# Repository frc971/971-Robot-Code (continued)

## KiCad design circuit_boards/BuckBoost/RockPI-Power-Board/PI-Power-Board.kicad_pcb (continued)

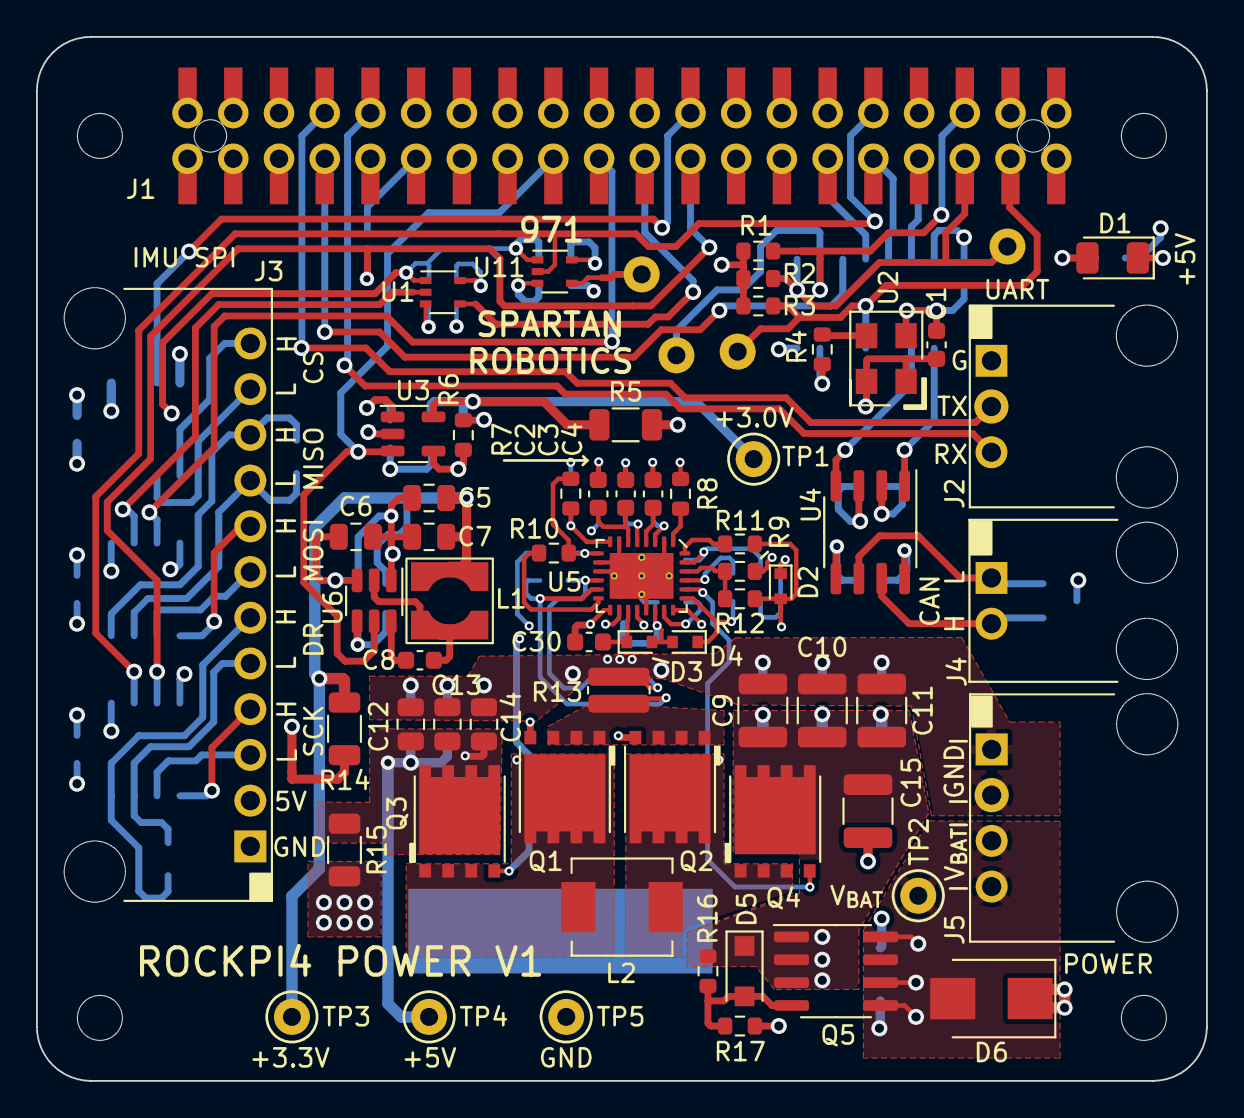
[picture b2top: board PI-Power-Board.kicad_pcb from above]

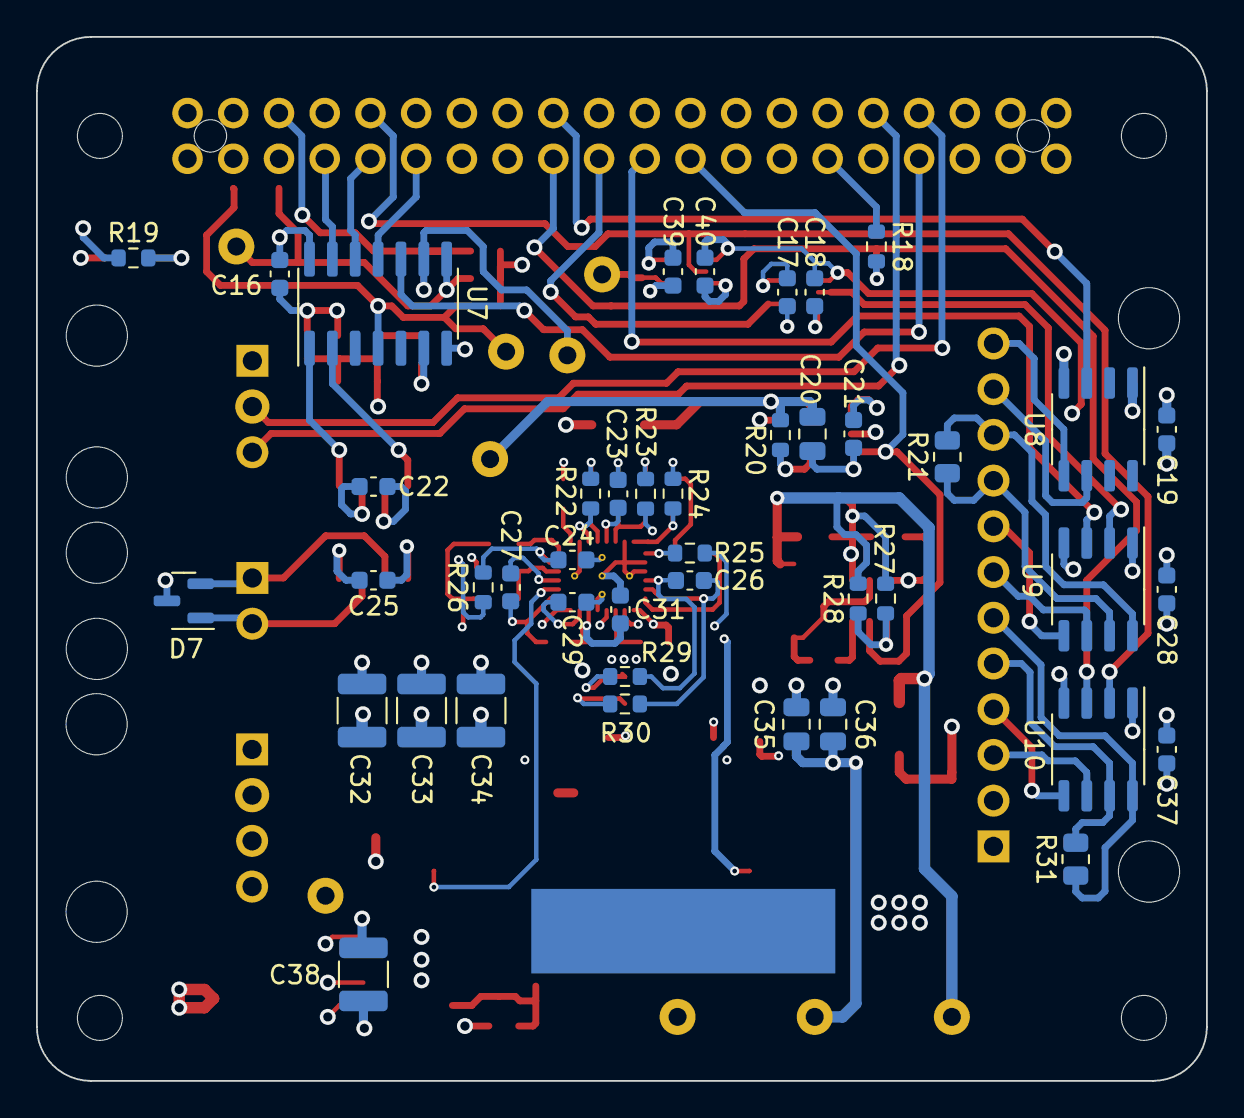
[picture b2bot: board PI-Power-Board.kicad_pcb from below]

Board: 4 copper layers, 65.0 x 58.0 mm, 118 parts (43 on the bottom side), 74 nets.

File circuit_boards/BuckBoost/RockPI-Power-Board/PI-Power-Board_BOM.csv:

Source:,/home/scottberman/Documents/Projects/FRC971/RKPI4-Power/PI-Power-Board/PI-Power-Board.kicad_sch,,,,
Date:,Tue 06 Dec 2022 05:25:53 PM PST,,,,
Tool:,Eeschema 6.0.9-8da3e8f707~117~ubuntu20.04.1,,,,
Generator:,/usr/share/kicad/plugins/bom_csv_grouped_by_value.py,,,,
Component Count:,103,,,,
,,,,,
Individual Components:,,,,,
,,,,,
,,,,,
Item,Qty,Reference(s),Value,MFG,MFG P/N
1,17,"C1, C8, C16, C17, C18, C19, C21, C22, C24, C25, C27, C28, C29, C30, C37, C39, C40",0.1uF-10%-50V-0603,Samsung Electro-Mechanics,CL10B104KB8NNNC
2,2,"C2, C23",0.015uF-10%-50V-0603,YAGEO,CC0603KRX7R9BB153
3,1,C3,330pF-5%-50V-0603,Murata,GCM1885C2A331FA16D
4,2,"C4, C26",47pF-5%-50V-0603,Samsung Electro-Mechanics,CL10C470JB8NNNC
5,9,"C5, C6, C7, C12, C13, C14, C20, C35, C36",22uF-10V-10%-0805,Samsung Electro-Mechanics,CL21A226KPCLRNC
6,8,"C9, C10, C11, C15, C32, C33, C34, C38",22uF-25V-10%-1210,Murata,GRM32ER61E226KE15L
7,1,C31,1.0uF-10%-10V-0603,Samsung Electro-Mechanics,CL10B105KP8NNNC
8,1,D1,+5V,Everlight Electronics Co Ltd,QTLP650D4TR
9,1,D2,NSR05T40XV2T5G,onsemi,NSR05T40XV2T5G
10,1,D3,NSR05T40XV2T5G,onsemi,NSR05T40XV2T5G
11,1,D4,NSR05T40XV2T5G,onsemi,NSR05T40XV2T5G
12,1,D5,15V,Nexperia,"BZT52H-C15,115"
13,1,D6,15V,Littelfuse,SZ1SMB15CAT3G
14,1,D7,PESD1CAN,Nexperia,"PESD1CAN,215"
15,1,J1,PI Header,Harwin Inc,M20-7812045
16,1,J2,UART,Molex,70555-0002
17,1,J3,IMU SPI,Molex,70555-0011
18,1,J4,CAN,Molex,70555-0001
19,1,J5,POWER,Molex,70555-0003
20,1,L1,2.5uH-1.45A,Wurth Electronik,744031002
21,1,L2,1.0 uH-13.7m-20%,Vishay,IHLP2020CZER1R0M01
22,4,"Q1, Q2, Q3, Q4",CSD17577Q5A,Texas Instruments,CSD17577Q5A
23,1,Q5,SI4483ADY-T1-GE3,Vishay,SI4483ADY-T1-GE3
24,5,"R1, R2, R3, R9, R23",2.00k-1%-0603,Yageo,RC0603FR-072KL
25,1,R4,49.9R-1%-0603,Yageo,RC0603FR-0749R9L
26,3,"R5, R14, R15",0R-1206,Yageo,RC1206JR-070RL
27,2,"R6, R20",DNI-0603,,
28,2,"R7, R11",105k-1%-0603,Yageo,RC0603FR-07105KL
29,1,R8,93.1k-1%-0603,Panasonic Electronic Components,ERJ-3EKF9312V
30,1,R10,10K0-1%-0603,Yageo,RC0603FR-0710KL
31,1,R12,249k-1%-0603,Yageo,RC0603FR-07249KL
32,1,R13,15m-1%-0612,"KOA Speer Electronics, Inc.",WU732BTTD15L0F
33,2,"R16, R24",20.0k-1%-0603,Yageo,RC0603FR-0720KL
34,2,"R17, R19",1.0k-1%-0603,Yageo,RC0603FR-071KL
35,1,R18,499R-1%-0603,Yageo,RC0603FR-07499RL
36,2,"R21, R31",120R-1%-0805,Yageo,RMCF0805FT120R
37,1,R22,15.8k-1%-0603,Yageo,RC0603FR-0715K8L
38,1,R25,0R-0603,Stackpole Electronics Inc,RMCF0603ZT0R00
39,1,R26,10R0-1%-0603,Yageo,RC0603FR-0710RL
40,1,R27,31.6k-1%-0603,Stackpole Electronics Inc,RMCF0603FT31K6
41,1,R28,10.0k-1%-0603,Yageo,RC0603FR-0710KL
42,2,"R29, R30",100R-1%-0603,Yageo,RC0603FR-07100RL
43,5,"TP1, TP2, TP3, TP4, TP5",,Keystone Electronics,5002
48,2,"U1, U11",NLSV1T34DFT2G,onsemi,NLSV1T34DFT2G
49,1,U2,40MHz,ECS Inc,ECS-5032MV-400-CN-TR
50,1,U3,MIC5233-3.0YM5-TR,Microchip,MIC5233-3.0YM5-TR
51,1,U4,MCP2542FD-E/SN,Microchip,MCP2542FD-E/SN
52,1,U5,LM5176RHF,Texas Instruments,LM5176RHFT
53,1,U6,AP62200WU-7,Diodes Inc,AP62200WU-7
54,1,U7,MCP2517FDT-H/SL,Microchip,MCP2517FDT-H/SL
55,3,"U8, U9, U10",ADM3490ARZ,Analog Devices,ADM3490ARZ

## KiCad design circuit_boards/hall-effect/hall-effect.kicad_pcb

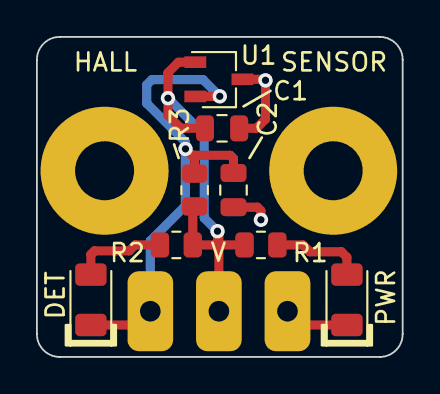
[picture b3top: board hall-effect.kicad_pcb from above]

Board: 2 copper layers, 20.3 x 17.8 mm, 11 parts (0 on the bottom side), 5 nets.

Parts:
C1: 0.1uF-25V-0805; C_0805_2012Metric
C2: 4.7nF-50V-0805; C_0805_2012Metric
D1: PWR; LED_1206_3216Metric
D2: DET; LED_1206_3216Metric
H1, H2: mounting-hole
J1: Conn_01x03_Male; 3PIN header
R1, R2: 1.0k-1%-0805; R_0805_2012Metric
R3: 10k-1%-0805; R_0805_2012Metric
U1: US5881LSE; TSOT-23

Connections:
/5V0: C1.1, J1.2, R1.1, R2.1, R3.1, U1.1 (VDD)
/GND: C1.2, C2.2, D1.1 (K), J1.1, U1.3 (GND)
/OUT: C2.1, D2.1 (K), J1.3, R3.2, U1.2 (OUT)
unnamed: D1.2 (A), R1.2
unnamed: D2.2 (A), R2.2

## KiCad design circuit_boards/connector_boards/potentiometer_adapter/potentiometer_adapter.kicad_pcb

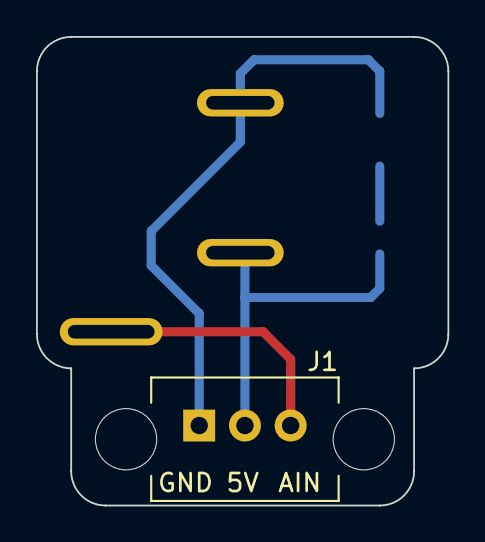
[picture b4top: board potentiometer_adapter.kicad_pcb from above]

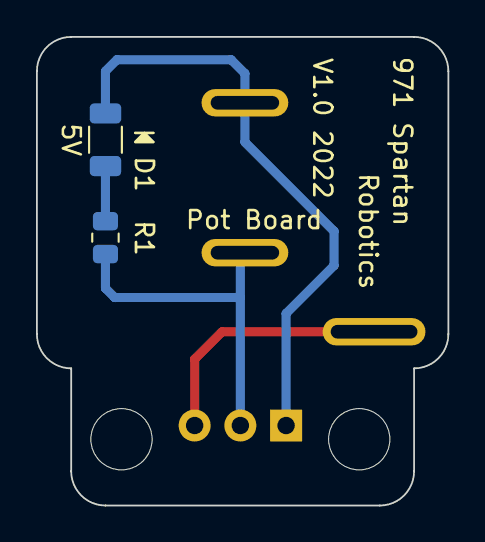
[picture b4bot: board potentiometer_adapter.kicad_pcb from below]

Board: 2 copper layers, 22.9 x 26.0 mm, 4 parts (2 on the bottom side), 4 nets.

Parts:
D1: 5V; R_1206_3216Metric
J1: Conn_01x03_Male; 70541-0037
R1: 2K 1%; R_0805_2012Metric
RV1: R_Potentiometer; Bourns3647

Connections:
/5V0: J1.2, R1.1, RV1.1
/AIN: J1.3, RV1.2
/GND: D1.1 (K), J1.1, RV1.3
unnamed: D1.2 (A), R1.2

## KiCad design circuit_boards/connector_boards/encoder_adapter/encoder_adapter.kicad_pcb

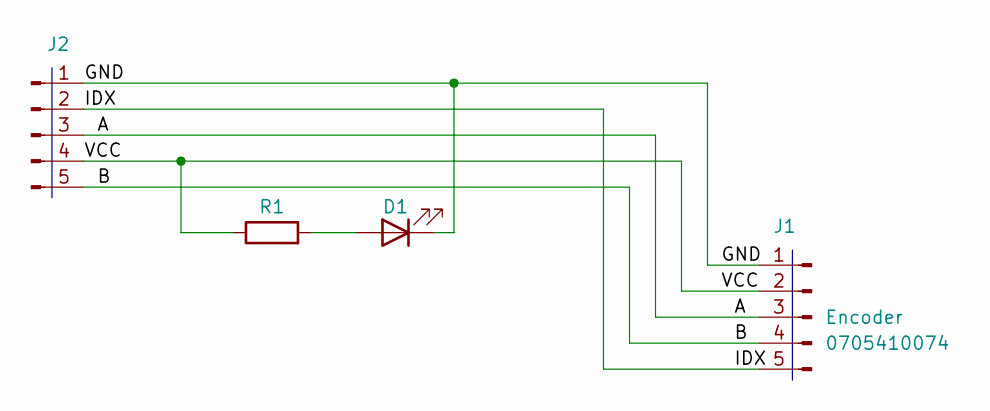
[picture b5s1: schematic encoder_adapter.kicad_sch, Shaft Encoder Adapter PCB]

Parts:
D1: LED; LED_1206_3216Metric; MFG P/N QTLP650D4TR
J1: Encoder; MOLEX_0705410074; MFG P/N 0705410074
J2: Conn_01x05_Male; PinHeader_1x05_P2.54mm_Vertical
R1: R; R_0805_2012Metric

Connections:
/A: J1.3, J2.3
/B: J1.4, J2.5
/GND: D1.1 (K), J1.1, J2.1
/IDX: J1.5, J2.2
/VCC: J1.2, J2.4, R1.1
unnamed: D1.2 (A), R1.2

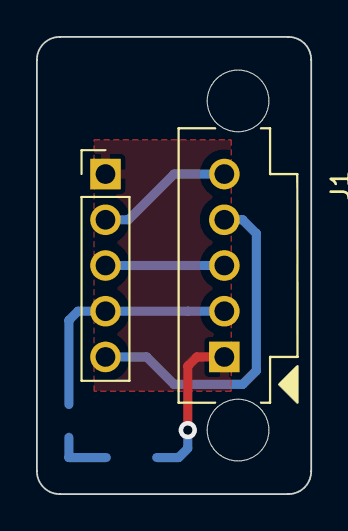
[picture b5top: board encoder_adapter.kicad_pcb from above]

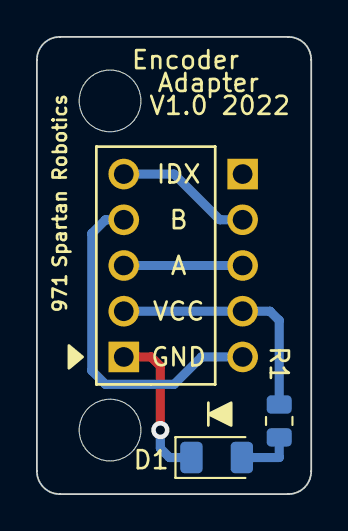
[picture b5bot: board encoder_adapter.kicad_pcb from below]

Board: 2 copper layers, 15.2 x 25.4 mm, 4 parts (2 on the bottom side), 6 nets.

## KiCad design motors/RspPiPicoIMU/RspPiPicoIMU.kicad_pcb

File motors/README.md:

# Driver station
## Setup
1. Install Teensy Loader [here](https://www.pjrc.com/teensy/loader_mac.html).

## Make changes
1. Most of the code lives in `/motors/driver_station*`.

## Deploy
1. Build driver station. This outputs a file `bazel-bin/motors/driver_station.hex`.
    ```shell
    bazel build -c opt --config=cortex-m4f //motors:driver_station
    ```

2. Send the file to your local development machine.
    ```shell
    scp <user@build.frc971.org>:917-Robot-Code/bazel-bin/motors/driver_station.hex ~/Downloads/driver_station.hex
    ```

3. Open hex file in Teensy loader. Press button on Teensy.

## Swerve
1. To allow a swerve controller to work, a jumper should be in the BTN17 spot (view schematics below).

## References
- Electrical schematics [here](https://github.com/frc971/electrical/blob/main/robots/2023/driver-station/DriverStation-8Apr2023.pdf).
- Joystick adc pin mapping[here](https://github.com/frc971/electrical/blob/main/robots/2025/Driver%20Station/Harness%20Drawings/TX16S-Joystick-Input.png).

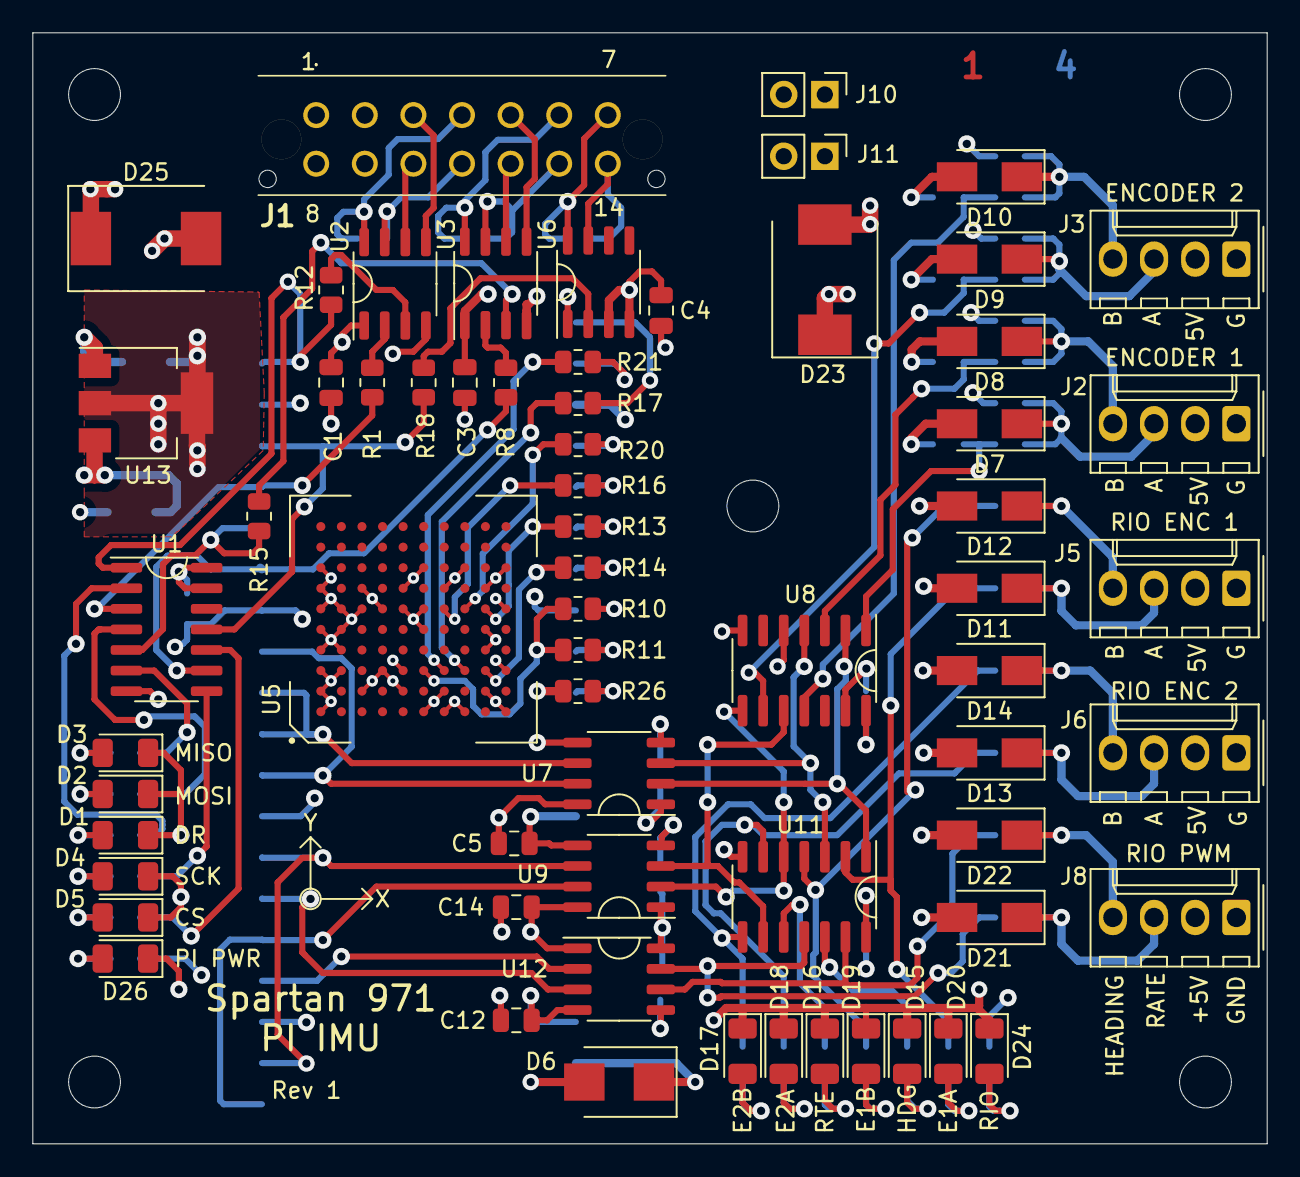
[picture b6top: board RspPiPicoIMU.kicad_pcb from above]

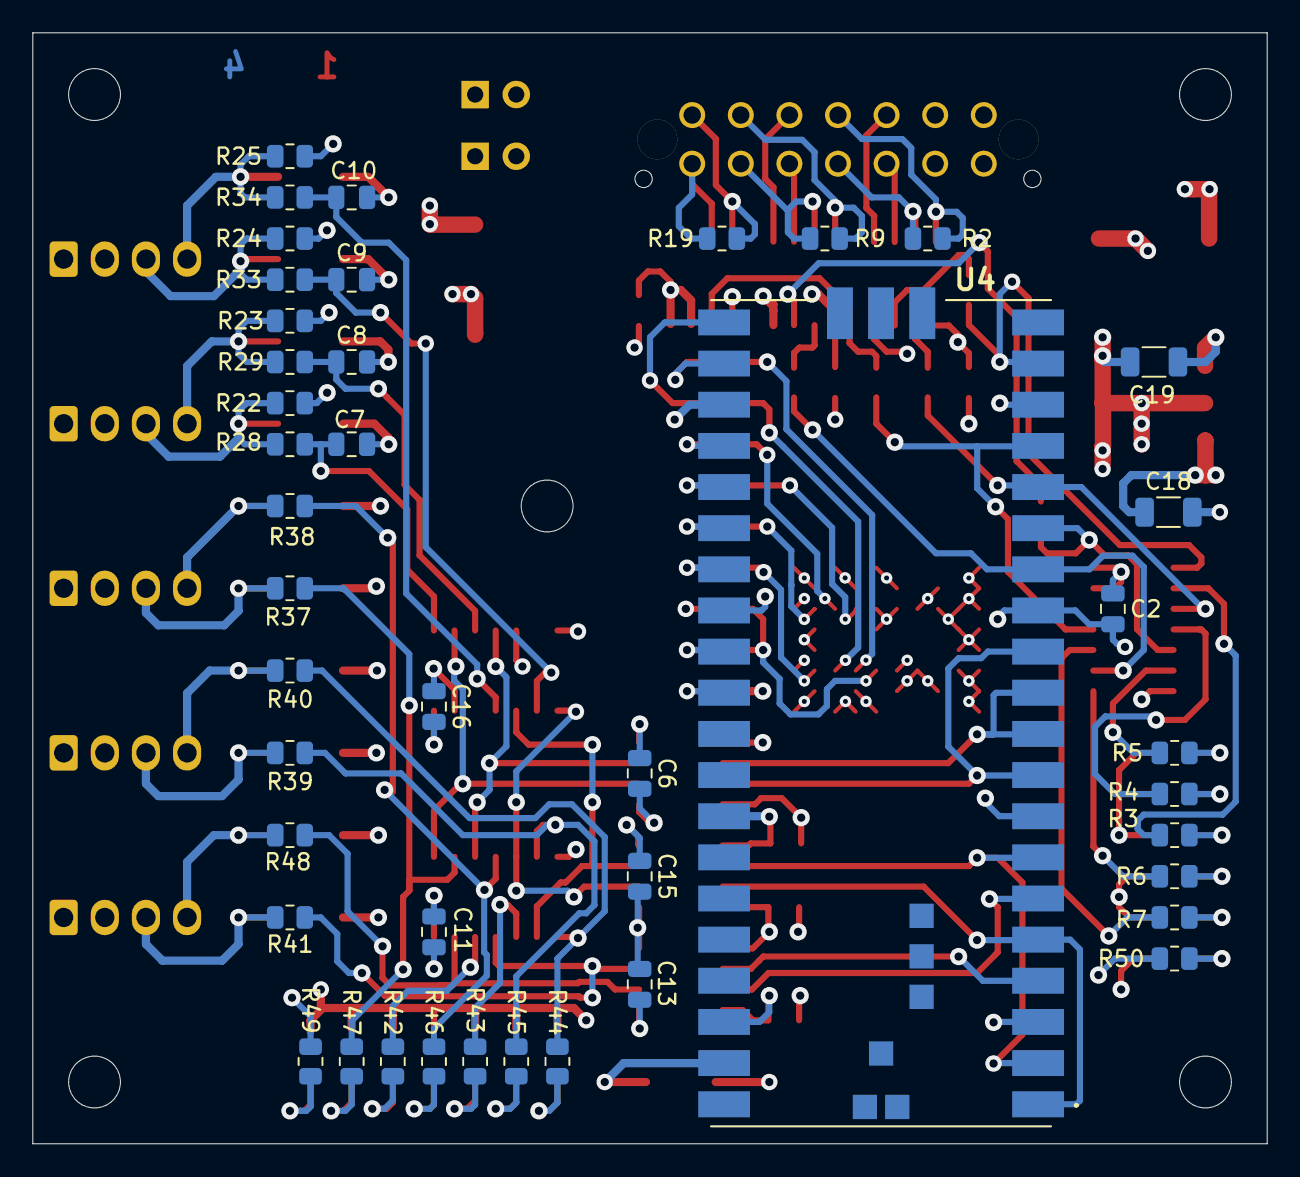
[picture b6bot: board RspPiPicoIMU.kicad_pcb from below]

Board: 4 copper layers, 76.2 x 68.6 mm, 113 parts (43 on the bottom side), 91 nets.

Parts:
C1, C2, C3, C4, C5, C6, C11, C12, C13, C14, C15, C16: 0.1uF; C_0805_2012Metric
C7, C8, C9, C10: 1.0nF; C_0805_2012Metric
C18, C19: 22uF; C_1206_3216Metric
D1: DR; LED_1206_3216Metric
D2: MOSI; LED_1206_3216Metric
D3: MISO; LED_1206_3216Metric
D4: SCK; LED_1206_3216Metric
D5: CS; LED_1206_3216Metric
D6: B240; D_SMB
D7, D8, D9, D10, D11, D12, D13, D14, D21, D22: SMA6J5.0A; D_SMA
D15: HDG; LED_1206_3216Metric
D16: RTE; LED_1206_3216Metric
D17: E2B; LED_1206_3216Metric
D18: E2A; LED_1206_3216Metric
D19: E1B; LED_1206_3216Metric
D20: E1A; LED_1206_3216Metric
D23, D25: SMDJ5.0A; D_SMC
D24: RIO; LED_1206_3216Metric
D26: PI PWR; LED_1206_3216Metric
H1, H2, H3, H4, H4#2: MountingHole M3; MountingHole_3.2mm_M3
J1: MICROFIT-VERT-2x7; Molex430451425
J2: ENCODER 1; Molex_KK-254_AE-6410-04A_1x04_P2.54mm_Vertical
J3: ENCODER 2; Molex_KK-254_AE-6410-04A_1x04_P2.54mm_Vertical
J5: RIO ENC 1; Molex_KK-254_AE-6410-04A_1x04_P2.54mm_Vertical
J6: RIO ENC 2; Molex_KK-254_AE-6410-04A_1x04_P2.54mm_Vertical
J8: RIO PWM; Molex_KK-254_AE-6410-04A_1x04_P2.54mm_Vertical
J10, J11: Conn_01x02_Male; PinHeader_1x02_P2.54mm_Vertical
R1, R8, R11, R12, R13, R14, R15, R16, R17, R18, R20, R21: 33R; R_0805_2012Metric
R2, R9, R19: 121R; R_0805_2012Metric
R3, R4, R5, R6, R7, R28, R29, R33, R34, R42, R43, R44, R45, R46, R47, R49, R50: 1.00K; R_0805_2012Metric
R10, R26: 4.99k; R_0805_2012Metric
R22, R23, R24, R25: 10.0k; R_0805_2012Metric
R37, R38, R39, R40, R41, R48: 100R; R_0805_2012Metric
U1, U8, U11: CD74ACT14M96; SO-14_3.9x8.65mm_P1.27mm
U2, U3, U6: ADM3490ARZ; SO-8_3.9x4.9mm_P1.27mm
U4: SC0915-PI-Pico; PICO
U5: ADIS16505-3BMLZ; BGA-100_10x10_15.0x15.0mm
U7, U9, U12: ADUM1280ARZ; SO-8_3.9x4.9mm_P1.27mm
U13: AZ1117IH-3.3TRG1; SOT-223

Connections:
+3V3: C1.1, C3.1, C4.1, C5.1, C12.1, C14.1, C19.2, R10.2, R26.2, U2.1, U3.1, U5.C7, U5.D6, U5.E3, U5.G1, U5.H1, U5.J4, U5.J5, U5.K6, U6.1, U7.8, U9.8, U12.1, U13.2, U13.4
+5V: C2.1, C18.2, D6.2, D25.1, J1.1, J1.2, J10.2, R50.2, U1.13, U1.14, U13.3
+5VD: C6.2, C11.2, C13.2, C15.2, C16.2, D23.1, J2.2, J3.2, J5.2, J6.2, J8.2, J10.1, R22.2, R23.2, R24.2, R25.2, R49.2, U7.1, U8.14, U9.1, U11.14, U12.8
/CS_H: J1.7, R19.1, U6.8
/CS_IMU: R21.2, U5.G3
/CS_L: J1.14, R19.2, U6.7
/CS_PIn: R18.2, U1.11, U4.17
/DIN_IMU: R16.2, U5.G6
/DOUT_IMU: R17.2, U5.H3
/DR_H: J1.3, U2.5
/DR_IMU: R13.2, U5.J6
/DR_L: J1.10, U2.6
/DR_PI: R12.1, U2.3
/EN1A: D7.1, J2.3, R22.1, R28.1
/EN1A-RIO: D11.1, J5.3, R37.1
/EN1B: D8.1, J2.4, R23.1, R29.1
/EN1B-RIO: D12.1, J5.4, R38.1
/EN2A: D9.1, J3.3, R24.1, R33.1
/EN2A-RIO: D13.1, J6.3, R39.1
/EN2B: D10.1, J3.4, R25.1, R34.1
/EN2B-RIO: D14.1, J6.4, R40.1
/ENC1-A: U4.9, U4.12, U7.7
/ENC1-B: U4.10, U4.11, U7.6
/ENC2-A: U4.1, U4.5, U9.7
/ENC2-B: U4.2, U4.7, U9.6
/HEADING_PWM: U4.6, U12.3
/HEADING_PWM_RIO: D22.1, J8.4, R48.1
/MISO_H: J1.5, U3.5
/MISO_L: J1.12, U3.6
/MISO_PI: R15.1, U3.3
/MOSI_H: J1.4, R2.1, U2.8
/MOSI_L: J1.11, R2.2, U2.7
/MOSI_PI: R1.2, U1.3, U4.16
/RATE-PWM-RIO: D21.1, J8.3, R41.1
/RATE_PWM: U4.4, U12.2
/RST_IMU: R10.1, R11.2, U5.F3
/SCK_H: J1.6, R9.1, U3.8
/SCK_L: J1.13, R9.2, U3.7
/SCK_PI: R8.2, U1.9, U4.14
/SCLK_IMU: R20.2, U5.H6
/SYNC_IMU: R14.2, U5.J3
GND: C1.2, C2.2, C3.2, C4.2, C5.2, C12.2, C14.2, C18.1, C19.1, D1.1, D2.1, D3.1, D4.1, D5.1, D25.2, D26.1, J1.8, J1.9, J11.2, U1.7, U2.4, U3.4, U4.3, U4.8, U4.13, U4.18, U4.23, U4.28, U4.33, U4.38, U5.A1, U5.A2, U5.A3, U5.A4, U5.A5, U5.A6, U5.A7, U5.A8, U5.B3, U5.B4, U5.B5, U5.B6, U5.C2, U5.C6, U5.D3, U5.E2, U5.E6, U5.E7, U5.F1, U5.F5, U5.F6, U5.F8, U5.G2, U5.G7, U5.H8, U5.J2, U5.J7, U5.K1, U5.K3, U5.K8, U6.3, U6.4, U7.5, U9.5, U12.4, U13.1
GNDD: C6.1, C7.1, C8.1, C9.1, C10.1, C11.1, C13.1, C15.1, C16.1, D7.2, D8.2, D9.2, D10.2, D11.2, D12.2, D13.2, D14.2, D15.1, D16.1, D17.1, D18.1, D19.1, D20.1, D21.2, D22.2, D23.2, D24.1, J2.1, J3.1, J5.1, J6.1, J8.1, J11.1, U7.4, U8.5, U8.7, U8.13, U9.4, U11.7, U12.5
unnamed: C7.2, R28.2, U8.1
unnamed: C8.2, R29.2, U8.3
unnamed: C9.2, R33.2, U8.9
unnamed: C10.2, R34.2, U8.11
unnamed: D1.2, R3.1
unnamed: D2.2, R4.1
unnamed: D3.2, R5.1
unnamed: D4.2, R6.1
unnamed: D5.2, R7.1
unnamed: D6.1, U4.39
unnamed: D15.2, R42.1
unnamed: D16.2, R43.1
unnamed: D17.2, R44.1
unnamed: D18.2, R45.1
unnamed: D19.2, R46.1
unnamed: D20.2, R47.1
unnamed: D24.2, R49.1
unnamed: D26.2, R50.1
unnamed: R1.1, U2.2
unnamed: R3.2, U1.2
unnamed: R4.2, U1.4
unnamed: R5.2, U1.6
unnamed: R6.2, U1.8
unnamed: R7.2, U1.10
unnamed: R8.1, U3.2
unnamed: R11.1, U4.29
unnamed: R12.2, U1.1, U4.19
unnamed: R13.1, U4.26
unnamed: R14.1, U4.27
unnamed: R15.2, U1.5, U4.15
unnamed: R16.1, U4.25
unnamed: R17.1, U4.21
unnamed: R18.1, U6.2
unnamed: R20.1, U4.24
unnamed: R21.1, U4.22
unnamed: R26.1, U4.30
unnamed: R37.2, R47.2, U11.2
unnamed: R38.2, R46.2, U11.4
unnamed: R39.2, R45.2, U11.6
unnamed: R40.2, R44.2, U11.8
unnamed: R41.2, U11.11, U12.7
unnamed: R42.2, U11.12
unnamed: R43.2, U11.10
unnamed: R48.2, U11.13, U12.6
unnamed: U7.2, U8.2, U11.1
unnamed: U7.3, U8.4, U11.3
unnamed: U8.8, U9.2, U11.5
unnamed: U8.10, U9.3, U11.9

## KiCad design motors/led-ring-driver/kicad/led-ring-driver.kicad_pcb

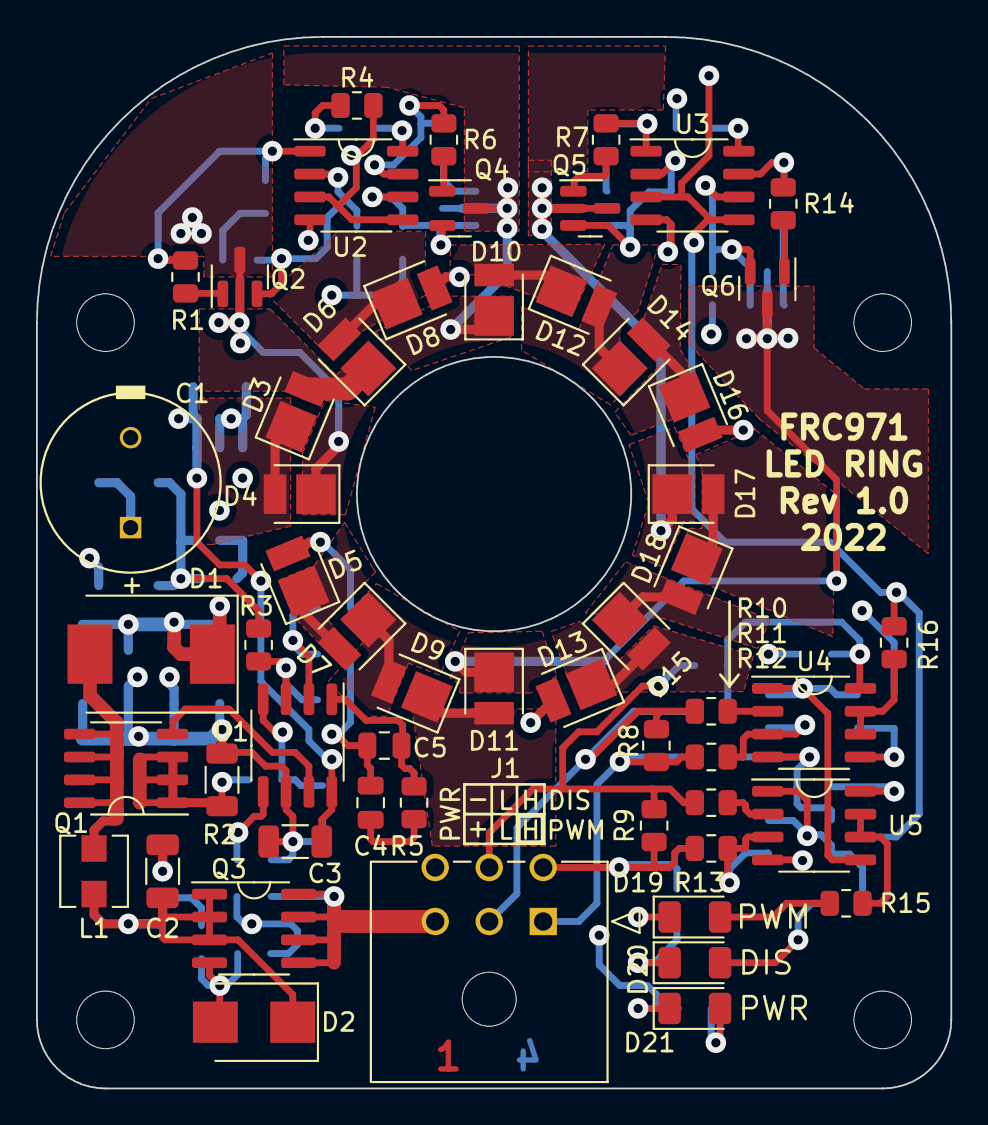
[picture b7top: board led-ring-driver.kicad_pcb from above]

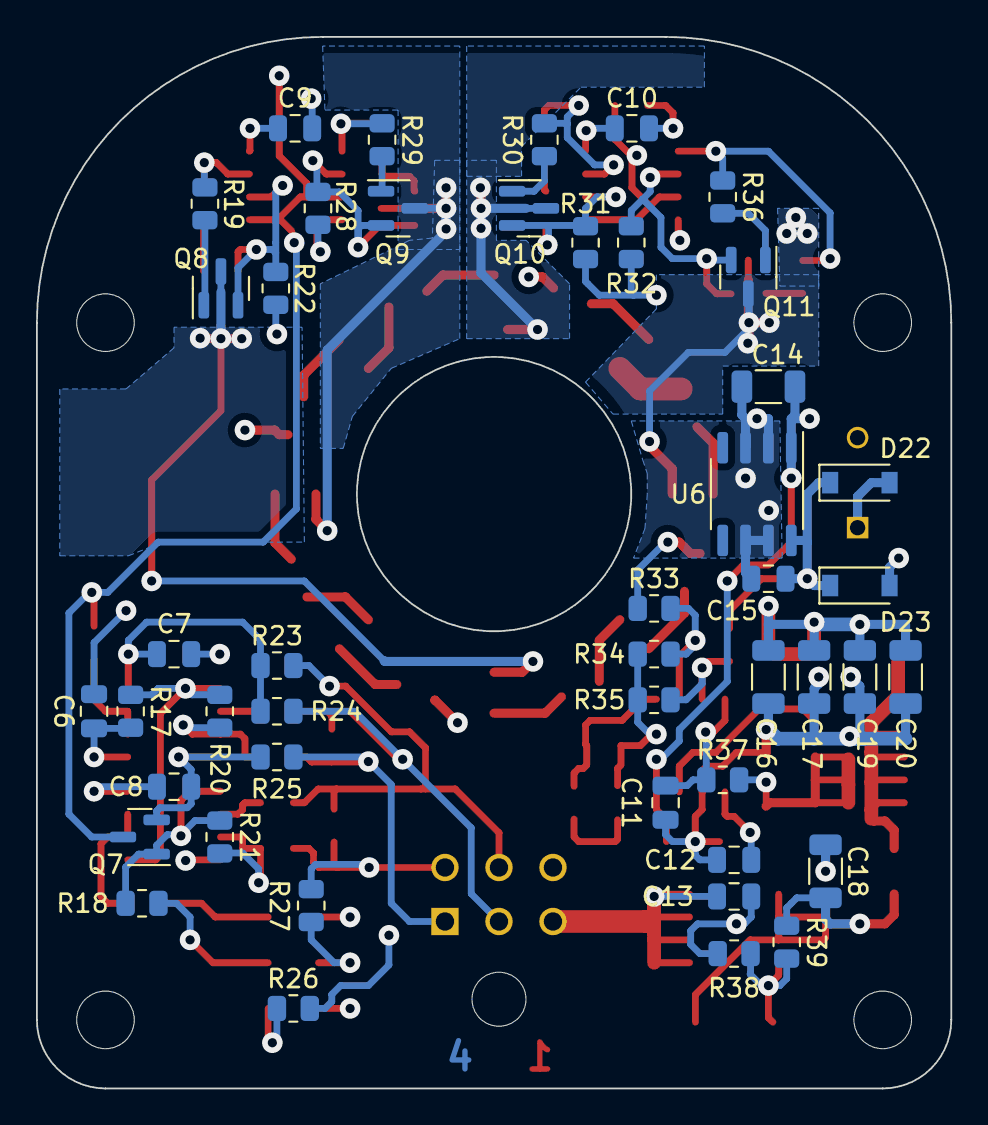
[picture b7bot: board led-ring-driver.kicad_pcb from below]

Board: 4 copper layers, 50.8 x 58.4 mm, 101 parts (46 on the bottom side), 65 nets.

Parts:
C1: 270uF 25V; CAPPRD500W60D1000H950
C2, C3, C14, C16, C17, C18, C19, C20: 10uF; C_1206_3216Metric
C4, C11: 470pF; C_0805_2012Metric
C5: DNI; C_0805_2012Metric
C6, C7, C8, C9, C10: 0.1uF; C_0805_2012Metric
C12, C13, C15: 1.0uF; C_0805_2012Metric
D1: B330-13-F; D_SMC
D2: 12V; D_SMB
D3, D4, D5, D6, D7, D8, D9, D10, D11, D12, D13, D14, D15, D16, D17, D18: GREEN; LED_PLCC_2835
D19: PWM; LED_1206_3216Metric
D20: DIS; LED_1206_3216Metric
D21: PWR; LED_1206_3216Metric
D22, D23: CDBW0520L-G; D_SOD-123
J1: 430450601
L1: 6.8uH; SRP3020C-1R0M
Q1: SI4116DY-T1-GE3; SO-8_3.9x4.9mm_P1.27mm
Q2, Q4, Q5, Q6, Q8, Q9, Q10, Q11: MMBT4401; SOT-23
Q3: SI4143DY-T1-GE3; SOIC-8_3.9x4.9mm_P1.27mm
Q7: 2N7002; SOT-23
R1, R6, R7, R14, R19, R29, R30, R36: 1.00k; R_0805_2012Metric
R2: 90m; R_1206_3216Metric
R3: 30.0k; R_0805_2012Metric
R4, R8, R9, R10, R11, R12, R13, R15, R18, R23, R24, R25, R27, R38: 1.0k; R_0805_2012Metric
R5: 30k; R_0805_2012Metric
R16: 9.09k; R_0805_2012Metric
R17, R20, R21: 100k; R_0805_2012Metric
R22, R28, R31, R32: 10.0R; R_0805_2012Metric
R26, R33, R35: 10k; R_0805_2012Metric
R34: 909R; R_0805_2012Metric
R37: 100R; R_0805_2012Metric
R39: 10.0k; R_0805_2012Metric
U1: MIC2196YM; SO-8_3.9x4.9mm_P1.27mm
U2, U3, U4, U5: TLV272QDRG4Q1; SO-8_3.9x4.9mm_P1.27mm
U6: TL751L05CD; SO-8_3.9x4.9mm_P1.27mm

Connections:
+5V: C3.1, C7.1, C8.1, C9.1, C10.1, C14.1, R23.1, R24.1, U1.8 (VIN), U2.8 (V+), U3.8 (V+), U4.8 (V+), U5.8 (V+), U6.1 (OUT)
/Boost Converter/+15V: C1.P, C16.1, C17.1, C19.1, C20.1, D1.1 (K), D5.2 (A), D8.2 (A), D13.2 (A), D16.2 (A), D22.2 (A), R26.2, R33.1
/Boost Converter/SW: D1.2 (A), L1.2, Q1.5 (D), Q1.6 (D), Q1.7 (D), Q1.8 (D)
/Boost Converter/V_P: C2.1, C18.1, D2.1 (K), D23.2 (A), L1.1, Q3.1 (S), Q3.2 (S), Q3.3 (S), R39.1
/DISABLE_H: J1.4, R9.1, R13.1, R27.1
/DISABLE_L: J1.5, R9.2, R12.1, R23.2
/LED1A: D3.1 (K), D4.2 (A)
/LED1B: D3.2 (A), D6.1 (K)
/LED1C: D6.2 (A), D8.1 (K)
/LED2A: D10.2 (A), D12.1 (K)
/LED2B: D12.2 (A), D14.1 (K)
/LED2C: D14.2 (A), D16.1 (K)
/LED3A: D17.2 (A), D18.1 (K)
/LED3B: D15.1 (K), D18.2 (A)
/LED3C: D13.1 (K), D15.2 (A)
/LED4A: D9.1 (K), D11.2 (A)
/LED4B: D7.1 (K), D9.2 (A)
/LED4C: D5.1 (K), D7.2 (A)
/LED Current Regulator/LED1_NEG: D4.1 (K), Q2.3 (C), Q11.3 (C)
/LED Current Regulator/LED2_NEG: D10.1 (K), Q4.3 (C), Q10.3 (C)
/LED Current Regulator/LED3_NEG: D17.1 (K), Q5.3 (C), Q9.3 (C)
/LED Current Regulator/LED4_NEG: D11.1 (K), Q6.3 (C), Q8.3 (C)
/PWM_H: J1.1, R8.1, R11.1, R25.1
/PWM_L: J1.2, R8.2, R10.1, R24.2
/VIN: C13.1, J1.3, Q3.5 (D), Q3.6 (D), Q3.7 (D), Q3.8 (D)
GND: C1.N, C2.2, C3.2, C4.2, C5.2, C6.2, C7.2, C8.2, C9.2, C10.2, C11.2, C12.2, C13.2, C14.2, C15.2, C16.2, C17.2, C18.2, C19.2, C20.2, D19.1 (K), D20.1 (K), D21.1 (K), J1.6, Q7.2 (S), R2.2, R4.1, R22.2, R25.2, R27.2, R28.2, R31.2, R32.2, R34.2, R35.2, R38.2, U1.6 (GND), U2.4 (V-), U3.4 (V-), U4.4 (V-), U5.4 (V-), U6.2 (GND), U6.3 (GND), U6.6 (GND), U6.7 (GND)
unnamed: C4.1, R5.2
unnamed: C5.1, R5.1, U1.1 (COMP)
unnamed: C6.1, R17.2, U4.5 (+)
unnamed: C11.1, R37.1, U1.4 (CS)
unnamed: C12.1, U1.5 (VDD)
unnamed: C15.1, D22.1 (K), D23.1 (K), R3.1, U6.8 (IN)
unnamed: D2.2 (A), Q3.4 (G), R38.1, R39.2
unnamed: D19.2 (A), R15.1
unnamed: D20.2 (A), R18.1
unnamed: D21.2 (A), R26.1
unnamed: Q1.1 (S), Q1.2 (S), Q1.3 (S), R2.1, R37.2
unnamed: Q1.4 (G), U1.7 (OUTN)
unnamed: Q2.1 (B), R1.2
unnamed: Q4.1 (B), R6.2
unnamed: Q5.1 (B), R7.2
unnamed: Q5.2 (E), Q9.2 (E), R28.1, U3.2 (-)
unnamed: Q6.1 (B), R14.2
unnamed: Q6.2 (E), Q8.2 (E), R22.1, U3.6 (-)
unnamed: Q7.1 (G), R18.2, R21.2, U5.1
unnamed: Q7.3 (D), R4.2, R16.2, U2.3 (+), U2.5 (+), U3.3 (+), U3.5 (+)
unnamed: Q8.1 (B), R19.2
unnamed: Q9.1 (B), R29.2
unnamed: Q10.1 (B), R30.2
unnamed: Q4.2 (E), Q10.2 (E), R31.1, U2.6 (-)
unnamed: Q11.1 (B), R36.2
unnamed: Q2.2 (E), Q11.2 (E), R32.1, U2.2 (-)
unnamed: R1.1, R36.1, U2.1
unnamed: R3.2, R35.1, U1.3 (EN/UVLO)
unnamed: R10.2, U4.2 (-)
unnamed: R11.2, R20.1, U4.3 (+)
unnamed: R12.2, U5.2 (-)
unnamed: R13.2, R21.1, U5.3 (+)
unnamed: R14.1, R19.1, U3.7
unnamed: R15.2, U5.6 (-), U5.7
unnamed: R16.1, U4.6 (-), U4.7
unnamed: R17.1, R20.2, U4.1, U5.5 (+)
unnamed: R7.1, R29.1, U3.1
unnamed: R6.1, R30.1, U2.7
unnamed: R33.2, R34.1, U1.2 (FB)

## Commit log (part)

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2024-09-23 Scouting app: fix action submission
    In the Review screen, ending the teleop phase showed up as "9" since it was not caught in the switch case in entry.ng.html. Additionally, if
    the scout switched between the endgame and review screen multiple times,
    there would be multiple penalty actions since the penalty action created
    when they went to the review page would not be deleted when they go back
    to the endgame screen. This patch addresses these problems.
2024-10-05 Add an experience buffer and tests.
    This sets us up to shard across the actor dimension and randomly sample
    actions.
2024-10-12 Set up control loops for y2024_swerve testing
2024-10-17 Fix nullptr dereference in dlqr()
2024-10-17 Cloning the repo tutorial changes
    I ran into a problem when I was following the tutorial to duplicate the repo.
    We tried to make the tutorial more specific on how to clone the repo
    and use the instructions on gerrit.
2024-10-19 Split Soft Actor-Criticl problem out into a class
    This sets us up to optimize multiple, different things.
2024-10-20 Add error message for no schema in aos/logging/config_remapper.cc
2024-10-26 Fix goal not being passed to gradient from data
2024-10-27 Put step number on top of LQR plots
    Makes it easier to tell when they update.
2024-10-27 Reorganize batched training functions in train.py
    By interleaving them with the actual logic, they were making it harder
    to see the logic.
2024-10-27 Quiet down printing while training
    All the debugging makes it hard to see what is happening.
2024-10-27 Add flag to scale target entropy.
    This helps change how much exploration to do compared to how much to do
    the optimal action. Less entropy, ie a larger scalar, means that we
    will explore less. This helps swerve not get stuck at the limits.
2024-10-27 Add flag to set initial alpha for SAC
    This makes it so we can start with the correct entropy relatively
    easily without having to do lots of gradient decent steps.
2024-10-27 Add papers we used to the code
2024-10-30 Update CTRE libraries to phoenix 6 alpha-2
2024-10-30 Add JoystickGoal option to swerve Goal message
2024-11-01 Template jacobian.h on Scalar type
    This makes it so that we can run numerical Jacobian calculations on
    single-precision floats when we want to.
2024-11-02 Switch to BGR input in threshold.cc
2024-11-02 Clean up timing labels
2024-11-02 More todo comments for potential optimizations
2024-11-05 Make threshold code templated on image format
    Remove it from the top level gpu detector. This simplifies the code a
    lot by removing a bunch of unneeded template code from the main detector
    class.
2024-11-09 cleanup
2024-11-18 Remove start_binary from robot_downloader
    Since ~2019, we haven't used the start_list.txt generated from start_binary. The processes are instead written in the aos_config. The removal is nice to avoid confusion.
2024-11-28 move codelab into subfolder
    We'd like to add more codelabs.
2024-11-30 Add generic EKF class
2024-12-01 Mark sandbox-breaking calibration test "manual"
    This test went outside of the bazel sandbox to try to locate files on
    the local filesystem; mark it manual to prevent it being run by default
    until we can move the log dependency into a proper dependendency.
    Also, make it so that we actually print out stdout/stderr from the
    process that was failing to make error messages clearer.
2024-12-06 Adding visualization tool for collected points during intrinsics Draw charuco points on the image
    Also, fixed issue with using hard-coded 640x480 image size
    Added ability to flip image (true by default) to make it more intuitive
    Bump reprojection error tolerance to 5.0, so we can at least save the intrinsics,
    but warn if error is > 2.0
    Add captions to show how many images are captured and whether pose estimate is valid
    Allow saving of images to folder, for later loading and processing.
2024-12-09 Fix copy-paste error
2024-12-12 Blind change to maybe transparently deal with endian issues for 16 bit images
2024-12-15 Add velocity dynamics-based EKF
    This provides a more principled estimator that can be used with the
    linear swerve controller.
    This does not directly provide estimation of X/Y states.
2024-12-19 Assorted cleanup in prep for pull request
2024-12-28 Create a linear velocity controller for swerve specifically
    This puts together some of the pieces created in prior commits to
    provide a simplistic LQR-based controller for controlling the velocity
    of a swerve drivebase.
2024-12-28 Add the yocto sysroot for arm64
2025-01-06 Add drivetrain priority setting to bot3
2025-01-06 Created a y2025 folder and copied boilerplate code
2025-01-07 add swerve to joystick
2025-01-12 Fixed documentation bug where user was directed to create ~/.ssh/aliases instead of ~/.ssh/config.
2025-01-12 Add elevator constants
    Constants added:
    * elevator set point constants
    * elevator PotAndAbsEncoderConstants (zeroing_constants and potentiometer_offset)
    * elevator encoder and pot ratios in constants.h
2025-01-13 Add elevator to wpilib_interface
    There are two elevator krakens so I named them elevator_one and elevator_two
2025-01-15 Add pivot WPILib interface
2025-01-15 Create ui for autonomous path planning
2025-01-15 Add pivot superstructure Add pivot superstructure test
2025-01-16 Add End Effector superstructure
2025-01-19 Lower apriltag pixel border
    I'm doing this now that we're using the 8 parameter model. The reason
    why this pixel border was so large before is because we couldn't trust
    the detections we get on the edge of the image. But now that we can
    detect them better we should be okay to turn this down.
2025-01-20 Create autonomous controller
2025-01-20 Add preliminary buttons to control superstructure
2025-01-21 Add swerve to y2024_bot3
2025-01-23 Add accel_weight to y2024_bot3
    Didn't get caught in buildkite, causing main to fail
2025-01-24 Update 2025 configs
2025-01-25 Add climber constants and flatbuffers
2025-01-25 Add climber superstructure
2025-01-25 Add auto_align to swerve controller
2025-01-25 Add new robot constants
2025-01-26 Update Driver Ranking and View Tabs
2025-01-28 Add y2025 swerve replay
2025-02-01 Add end_effector wpilib
2025-02-01 Add notes to webserver
2025-02-05 Add schema checker to AOS config
    The aos_config flattener did not check we had a schema for each channel
    so when on the robot, things like aos_dump crash. This is a very easy
    thing to miss especially for new people(like I did) and the segfault
    is very cryptic so this should help with that. Also, fix broken ones.
2025-02-06 Fix --config=roborio
2025-02-08 Create visualizer for AprilTag locations
2025-02-08 Add 2025 localizer
    The goal of this is to give us robust localization on the field this
    year, but because we haven't done full localization with swerve yet
    we're implementing it using wpilib, weighted averaging, and a kalman
    filter. More is explained in the comment in localizer.h
    This also removes the x, y, and theta estimation in naive_estimator. It
    no longer outputs x and y and the theta it uses for correction in the
2025-02-08 Correct wrist constants
2025-02-09 Add auto align
2025-02-09 Make auto align latch
2025-02-09 implement auto align into swerve_control_loops.cc
2025-02-10 Update wpilib_interface for wrist
2025-02-10 Update constants and add more goals and update joysticks
2025-02-11 Tune auto align PID parameters
    Changes from 02.10 drive practice
2025-02-11 Add climbing
    This adds proper joystick goals for climbing and makes it current
    controlled.
2025-02-12 Slow down omega
2025-02-12 Add Notes and View Tabs
2025-02-13 Update constants
2025-02-15 Update constants for elevator and joystick_reader
2025-02-15 Update autonomous_controller to use the localizer
    This also makes some other minor changes like tuning the position gain
    on the PID and adding a test spline we used for making sure this worked
    during 02/13 drive practice.
2025-02-15 Add algae goals
2025-02-16 Add camera focus binary
    The idea of this binary is to load it on the orin but only as a utility
    to help focus the cameras. So, it's not going to be running be default.
    A higher number is a "more" focused camera, sent via LOG(INFO).
2025-02-17 Make robot choose front/back scoring based on localization
2025-02-17 Add infrastructure for 2025 autonomous actions
2025-02-17 Update auto align to be a bit slower
    This also makes it work with the software bot, which currently does not
    care about left and right yet.
2025-02-18 Make HP_locations snake case
2025-02-18 Negate x and y when on red alliance
2025-02-20 Add a more stable option for the ekf
2025-02-22 Update eigen to version 3.4.90
    Ran `./doc/allwpilib_subtree.sh add third_party/eigen_test https://gitlab.com/libeigen/eigen master`
    Fixes due to updating
    * Updated third_party/eigen/BUILD to have headers from `Eigen/src/plugins/**`
    * Suppressed deprecated warnings in //y2017/vision:target_finder
    * Removed unused variable in y2024/localizer/localizer.h
    * Removed unused variable in y2023/localizer/localizer.h
2025-02-22 Re order calibration and intrinsics to match robot
    The cameras swapped sides, this commit updates the camera ids and
    intrinsics to match that.
2025-02-22 Data Entry fixes
    Fix undo after scored coral, add dropped to pick up.
    Fix l1-l4 design.
2025-02-23 Do better error handling in led indicator
2025-02-23 Fix an unneeded LOG(INFO)
2025-02-25 Add auto align d loop and theta lock, and update localization
2025-02-25 Update joysticks for new swerve controller
2025-02-25 Fix Entry Undo and Revive
2025-02-25 Separate steer and drive current
2025-02-25 Add closest theta auto align
2025-02-26 Small fixes from 02.25
2025-02-27 Add velocity error to autonomous controller
2025-02-27 Fix actions breaking when a new section is added
2025-02-28 Let spit l1 voltage be different from spit voltage
2025-03-01 Pivot/Elevator moves first
    Add collision avoidance with reef
2025-03-01 Add flip to autonomous webui and add more autos
2025-03-02 Add climb set point for elevator, pivot, and wrist
2025-03-02 Add Frame Logger
    This is a binary on the orins which allows you to log frames captured
    from the camera at regular intervals specified as dt in the file.
2025-03-03 Add Barge and Processor Auto Orient
2025-03-04 Tune up subsystems
2025-03-04 Hardcode 20s to run for autos
2025-03-04 Add algae ground buttons and goal
2025-03-05 Make naive estimator use autonomous init
2025-03-06 Update View Tab
2025-03-09 Reset Penalties
2025-03-15 Add deadband to controller
2025-03-15 Add user button to swerve control loops
2025-03-15 Small button changes
2025-03-15 Zero Wrist
2025-03-19 change elevator zero
2025-03-21 Add Elevator and Pivot IK
2025-03-26 Actually correct mass and moi
2025-03-27 Use Can Ranges in y2025
2025-04-01 Use correct noise in kalman filter localizer
2025-04-01 Auto align reef collision avoidance
    Goes to a pose offset from the final goal pose first, then goes to
    final pose.
2025-04-10 Make Entry+Ranking Navigation Easier
